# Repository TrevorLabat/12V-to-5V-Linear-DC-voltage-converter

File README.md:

# 12V-to-5V-Linear-DC-voltage-converter
Gold Rush Robotics projects contributions

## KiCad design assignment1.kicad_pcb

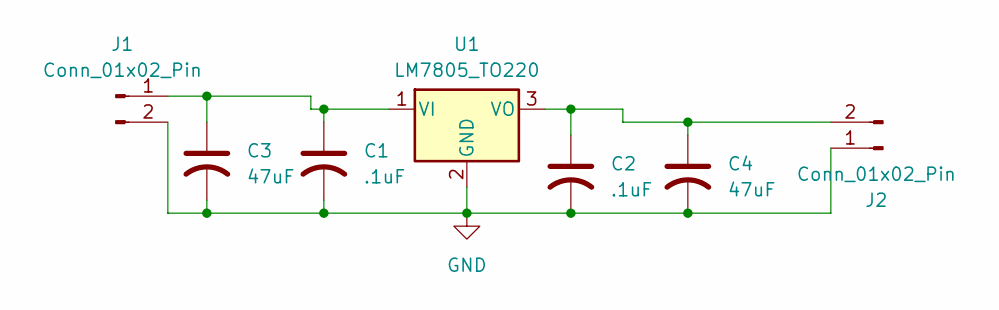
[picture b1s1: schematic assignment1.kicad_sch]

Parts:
C1, C2: .1uF; C_0805_2012Metric
C3, C4: 47uF; C_Radial_D6.3mm_H5.0mm_P2.50mm
J1, J2: Conn_01x02_Pin; TerminalBlock_Phoenix_MKDS-1,5-2-5.08_1x02_P5.08mm_Horizont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
U1: LM7805_TO220; TO-220-3_Vertical

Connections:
GND: C1.2, C2.2, C3.2, C4.2, J1.2, J2.1, U1.2 (GND)
unnamed: C1.1, C3.1, J1.1, U1.1 (VI)
unnamed: C2.1, C4.1, J2.2, U1.3 (VO)

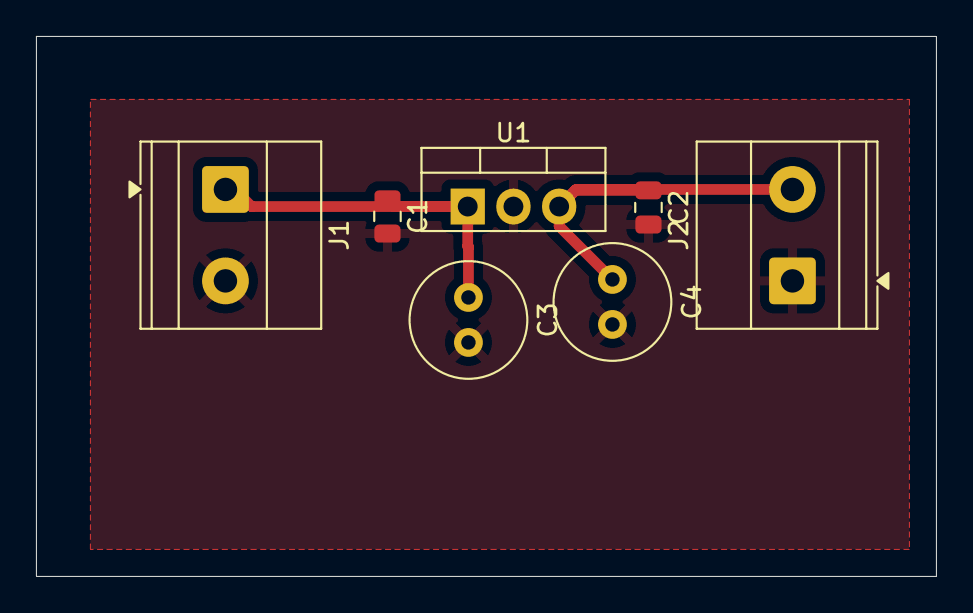
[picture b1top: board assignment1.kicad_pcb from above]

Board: 2 copper layers, 50.0 x 30.0 mm, 7 parts (0 on the bottom side), 3 nets.

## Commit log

2025-10-15 Test Assignment
